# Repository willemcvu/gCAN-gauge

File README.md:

# gCAN-gauge
An open-source ESP32-based programmable digital gauge targeted at EV conversions

See some previews of mechanical stuff and BOM costing here: https://imgur.com/gallery/dh8G9dV/comment/2116424201

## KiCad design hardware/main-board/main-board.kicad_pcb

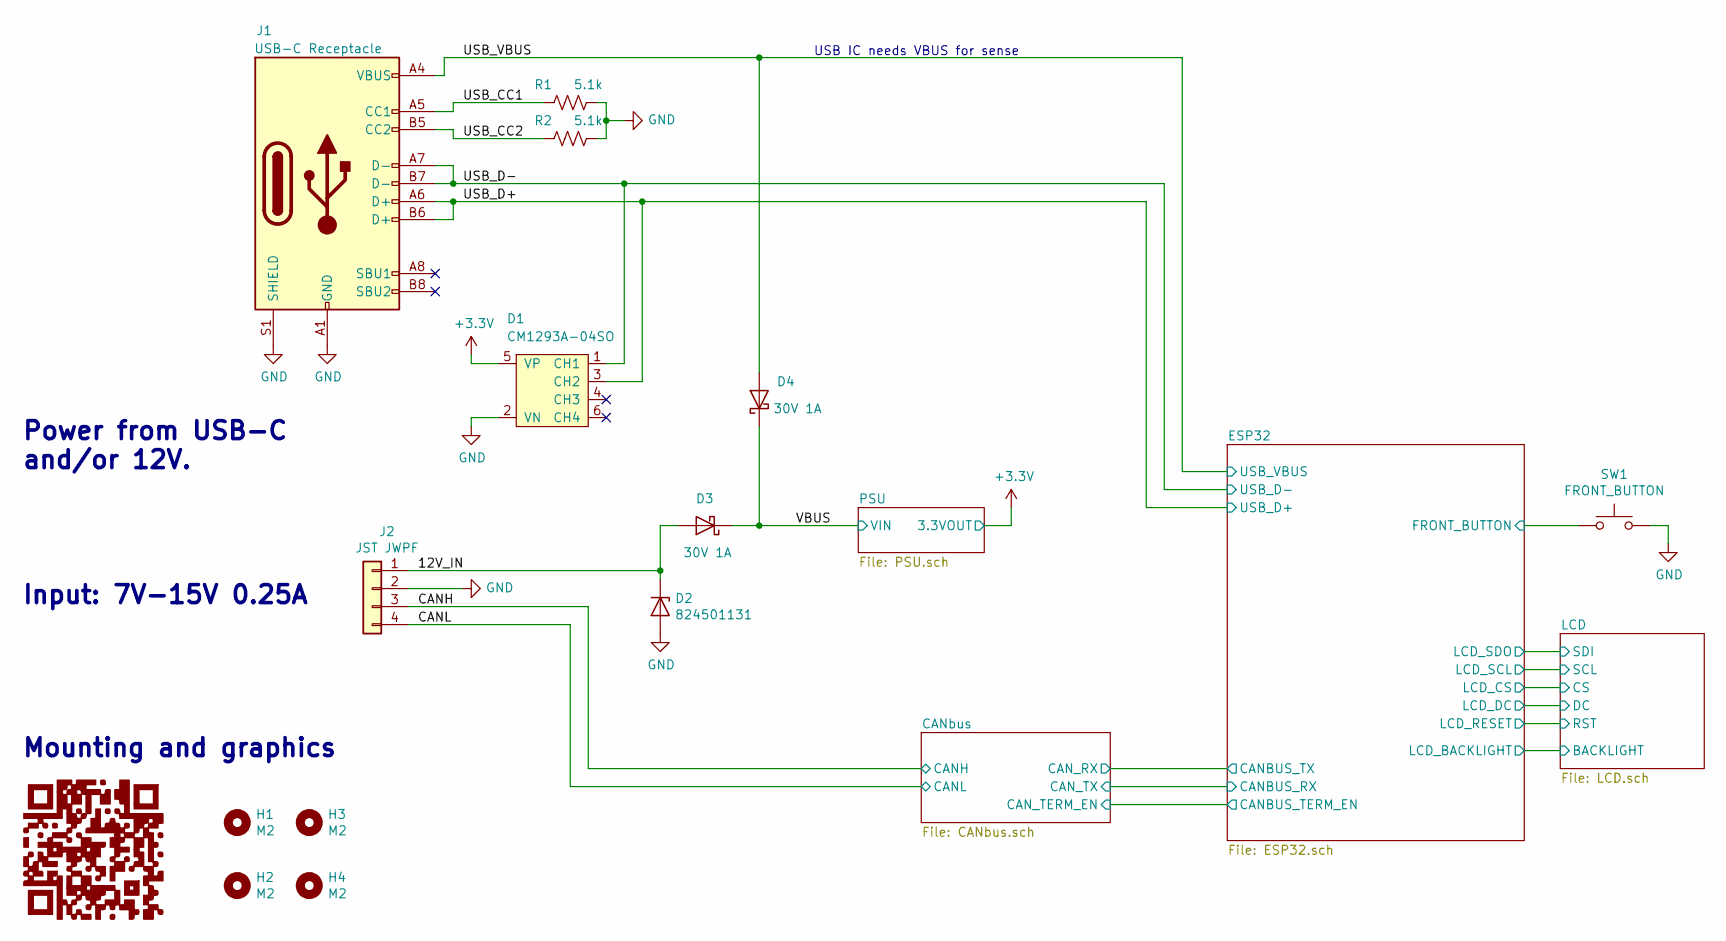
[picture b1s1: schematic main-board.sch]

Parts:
D1: CM1293A-04SO; SOT-23-6; MPN CM1293A-04SO
D2: 824501131; D_SMA; MPN 824501131
D3, D4: 30V 1A; D_SMA; MPN SS13MHRSG
G1: LOGO; gcan-gauge-github-link-qr; MPN DNP
H1, H2, H3, H4: M2; MountingHole_2.1mm; MPN DNP
J1: USB-C Receptacle; USB_C_Receptacle_JAE_DX07S024WJ3R400; MPN DX07S024WJ3R400
J2: JST JWPF; JST_JWPF_B04B-JWPF-SK-R_1x04_P2.00mm_Vertical; MPN B04B-JWPF-SK-R(LF)(SN)
R1, R2: 5.1k; R_0603_1608Metric; MPN RC0603JR-075K1L
SW1: FRONT_BUTTON; SW_SPST_PTS810; MPN B3S-1100P

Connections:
+3V3: D1.5 (VP); also elsewhere on the board
/12V_IN: D2.1 (K), D3.2 (A), J2.1
/CANH: J2.3; also elsewhere on the board
/CANL: J2.4; also elsewhere on the board
/ESP32/FRONT_BUTTON: SW1.1; also elsewhere on the board
/USB_CC1: J1.A5 (CC1), R1.2
/USB_CC2: J1.B5 (CC2), R2.2
/USB_D+: D1.3 (CH2), J1.A6 (D+), J1.B6 (D+); also elsewhere on the board
/USB_D-: D1.1 (CH1), J1.A7 (D-), J1.B7 (D-); also elsewhere on the board
/USB_VBUS: D4.2 (A), J1.A4 (VBUS), J1.A9 (VBUS), J1.B4 (VBUS), J1.B9 (VBUS); also elsewhere on the board
/VBUS: D3.1 (K), D4.1 (K); also elsewhere on the board
GND: D1.2 (VN), D2.2 (A), J1.A1 (GND), J1.A12 (GND), J1.B1 (GND), J1.B12 (GND), J1.S1 (SHIELD), J2.2, R1.1, R2.1, SW1.2; also elsewhere on the board

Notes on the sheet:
Input: 7V-15V 0.25A
Power from USB-C and/or 12V.
Mounting and graphics
USB IC needs VBUS for sense

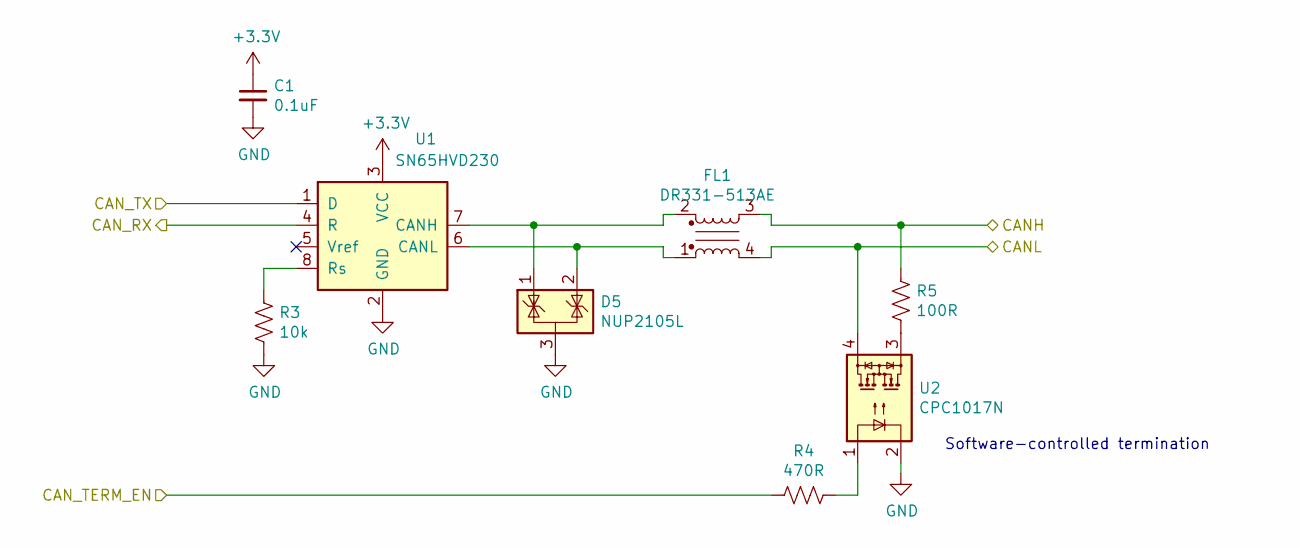
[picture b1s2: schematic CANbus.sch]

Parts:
C1: 0.1uF; C_0603_1608Metric; MPN CL10B104KA8NFNC
D5: NUP2105L; SOT-23; MPN NUP2105LT1G
FL1: DR331-513AE; COMMON_MODE_CHOKE_BOURNS_DR331; MPN DR331-513AE
R3: 10k; R_0603_1608Metric; MPN RC0603JR-0710KL
R4: 470R; R_0603_1608Metric; MPN RC0603JR-07470RL
R5: 100R; R_0603_1608Metric; MPN RC0603JR-07100RL
U1: SN65HVD230; SOIC-8_3.9x4.9mm_P1.27mm; MPN SN65HVD230
U2: CPC1017N; SOP-4_3.8x4.1mm_P2.54mm; MPN CPC1017N

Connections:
+3V3: C1.1, U1.3 (VCC); also elsewhere on the board
/CANH: FL1.3, R5.1; also elsewhere on the board
/CANL: FL1.4, U2.4; also elsewhere on the board
/ESP32/CANBUS_RX: U1.1 (D); also elsewhere on the board
/ESP32/CANBUS_TERM_EN: R4.2; also elsewhere on the board
/ESP32/CANBUS_TX: U1.4 (R); also elsewhere on the board
GND: C1.2, D5.3 (A), R3.2, U1.2 (GND), U2.2; also elsewhere on the board
unnamed: D5.1 (K), FL1.2, U1.7 (CANH)
unnamed: D5.2 (K), FL1.1, U1.6 (CANL)
unnamed: R3.1, U1.8 (Rs)
unnamed: R4.1, U2.1
unnamed: R5.2, U2.3

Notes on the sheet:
Software-controlled termination

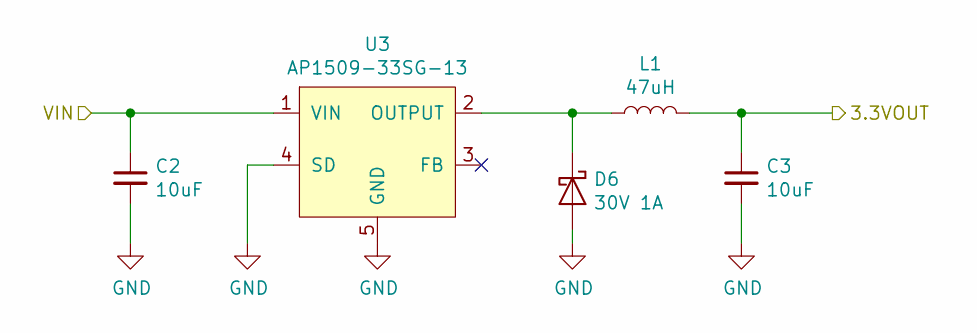
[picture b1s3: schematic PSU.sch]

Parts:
C2: 10uF; C_1210_3225Metric; MPN C1210C106M3RACTU
C3: 10uF; C_0805_2012Metric; MPN CL21B106KQQNFNE
D6: 30V 1A; D_SMA; MPN SS13MHRSG
L1: 47uH; L_Taiyo-Yuden_NR-60xx; MPN NRS6045T470MMGKV
U3: AP1509-33SG-13; SO-8_3.9x4.9mm_P1.27mm; MPN AP1509-33SG-13

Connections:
+3V3: C3.1, L1.2; also elsewhere on the board
/VBUS: C2.1, U3.1 (VIN); also elsewhere on the board
GND: C2.2, C3.2, D6.2 (A), U3.4 (SD), U3.5 (GND), U3.6 (GND), U3.7 (GND), U3.8 (GND); also elsewhere on the board
unnamed: D6.1 (K), L1.1, U3.2 (OUTPUT)

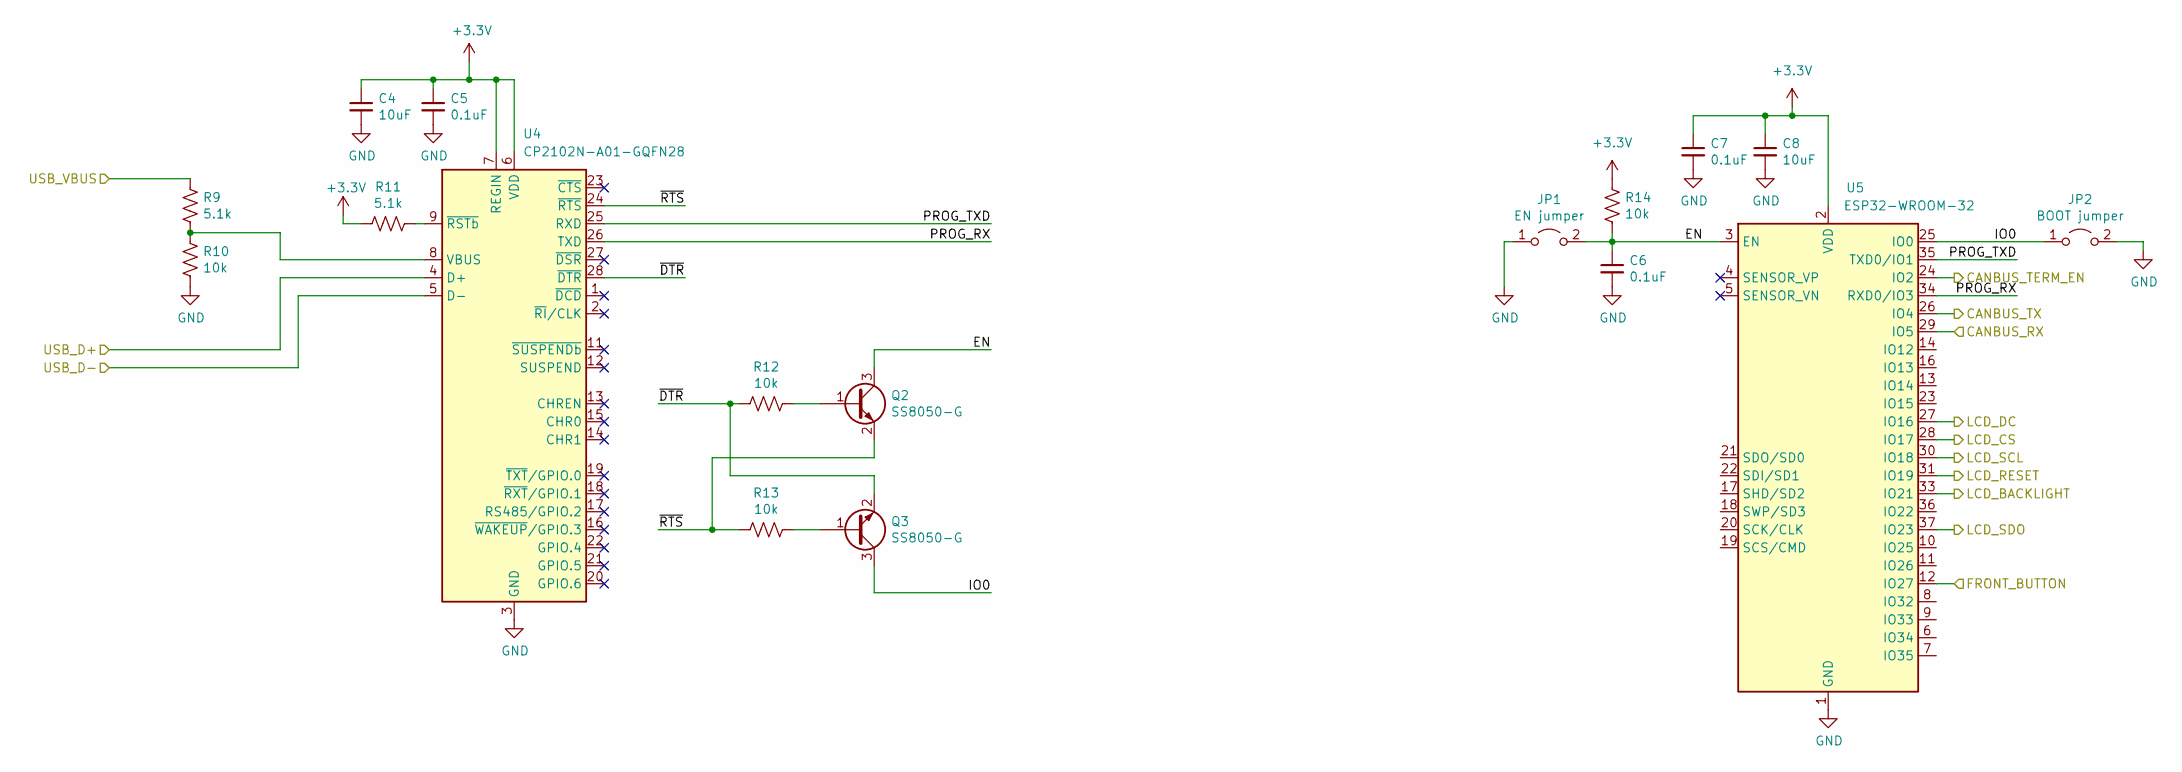
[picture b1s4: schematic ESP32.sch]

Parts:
C4, C8: 10uF; C_0805_2012Metric; MPN CL21B106KQQNFNE
C5, C6, C7: 0.1uF; C_0603_1608Metric; MPN CL10B104KA8NFNC
JP1: EN jumper; SolderJumper-2_P1.3mm_Open_RoundedPad1.0x1.5mm; MPN DNP
JP2: BOOT jumper; SolderJumper-2_P1.3mm_Open_RoundedPad1.0x1.5mm; MPN DNP
Q2, Q3: SS8050-G; SOT-23; MPN SS8050-G
R9, R11: 5.1k; R_0603_1608Metric; MPN RC0603JR-075K1L
R10, R12, R13, R14: 10k; R_0603_1608Metric; MPN RC0603JR-0710KL
U4: CP2102N-A01-GQFN28; QFN-28-1EP_5x5mm_P0.5mm_EP3.35x3.35mm; MPN CP2102N-A01-GQFN28
U5: ESP32-WROOM-32; MPN ESP32-WROOM-32D

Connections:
+3V3: C4.1, C5.1, C7.1, C8.1, R11.2, R14.1, U4.6 (VDD), U4.7 (REGIN), U5.2 (VDD); also elsewhere on the board
/ESP32/CANBUS_RX: U5.29 (IO5); also elsewhere on the board
/ESP32/CANBUS_TERM_EN: U5.24 (IO2); also elsewhere on the board
/ESP32/CANBUS_TX: U5.26 (IO4); also elsewhere on the board
/ESP32/EN: C6.1, JP1.2 (B), Q2.3 (C), R14.2, U5.3 (EN)
/ESP32/FRONT_BUTTON: U5.12 (IO27); also elsewhere on the board
/ESP32/IO0: JP2.1 (A), Q3.3 (C), U5.25 (IO0)
/ESP32/LCD_RESET: U5.31 (IO19); also elsewhere on the board
/ESP32/LCD_SCL: U5.30 (IO18); also elsewhere on the board
/ESP32/LCD_SDO: U5.37 (IO23); also elsewhere on the board
/ESP32/PROG_RX: U4.26 (TXD), U5.34 (RXD0/IO3)
/ESP32/PROG_TXD: U4.25 (RXD), U5.35 (TXD0/IO1)
/ESP32/~DTR: Q3.2 (E), R12.2, U4.28 (~DTR)
/ESP32/~RTS: Q2.2 (E), R13.2, U4.24 (~RTS)
/LCD/BACKLIGHT: U5.33 (IO21); also elsewhere on the board
/LCD/CS: U5.28 (IO17); also elsewhere on the board
/LCD/DC: U5.27 (IO16); also elsewhere on the board
/USB_D+: U4.4 (D+); also elsewhere on the board
/USB_D-: U4.5 (D-); also elsewhere on the board
/USB_VBUS: R9.2; also elsewhere on the board
GND: C4.2, C5.2, C6.2, C7.2, C8.2, JP1.1 (A), JP2.2 (B), R10.1, U4.3 (GND), U4.29 (GND), U5.1 (GND), U5.15 (GND), U5.38 (GND); also elsewhere on the board
unnamed: Q2.1 (B), R12.1
unnamed: Q3.1 (B), R13.1
unnamed: R9.1, R10.2, U4.8 (VBUS)
unnamed: R11.1, U4.9 (~RSTb)

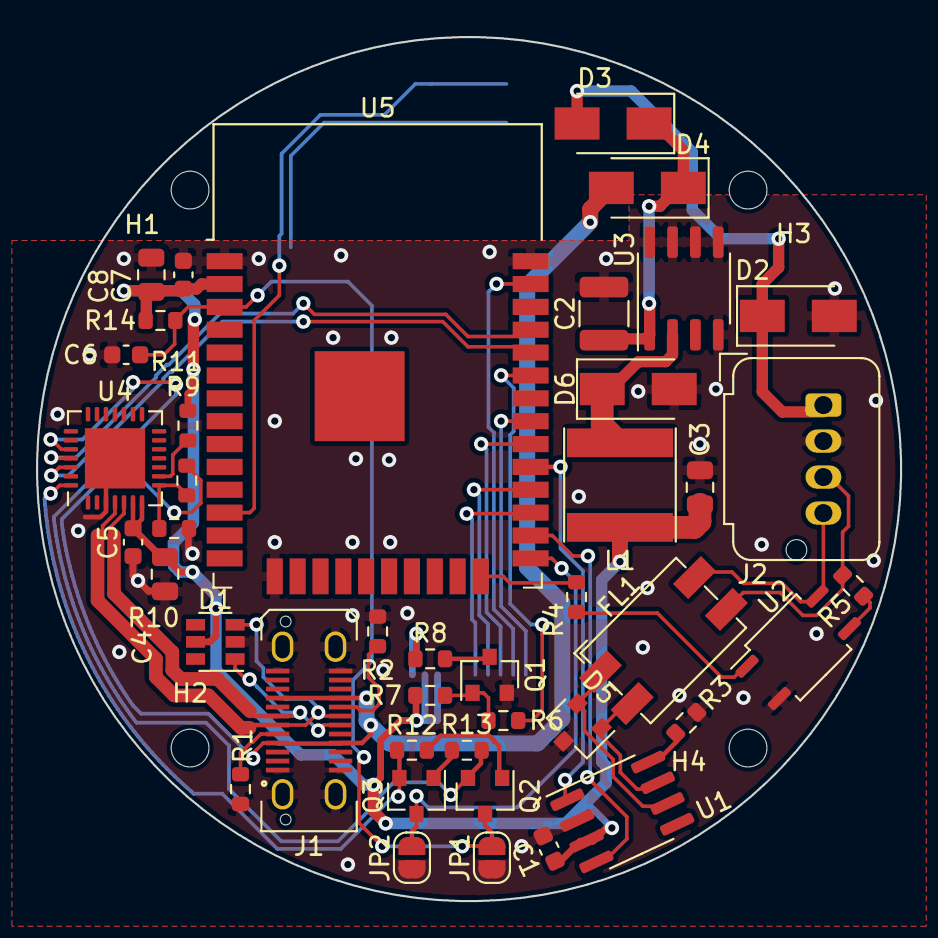
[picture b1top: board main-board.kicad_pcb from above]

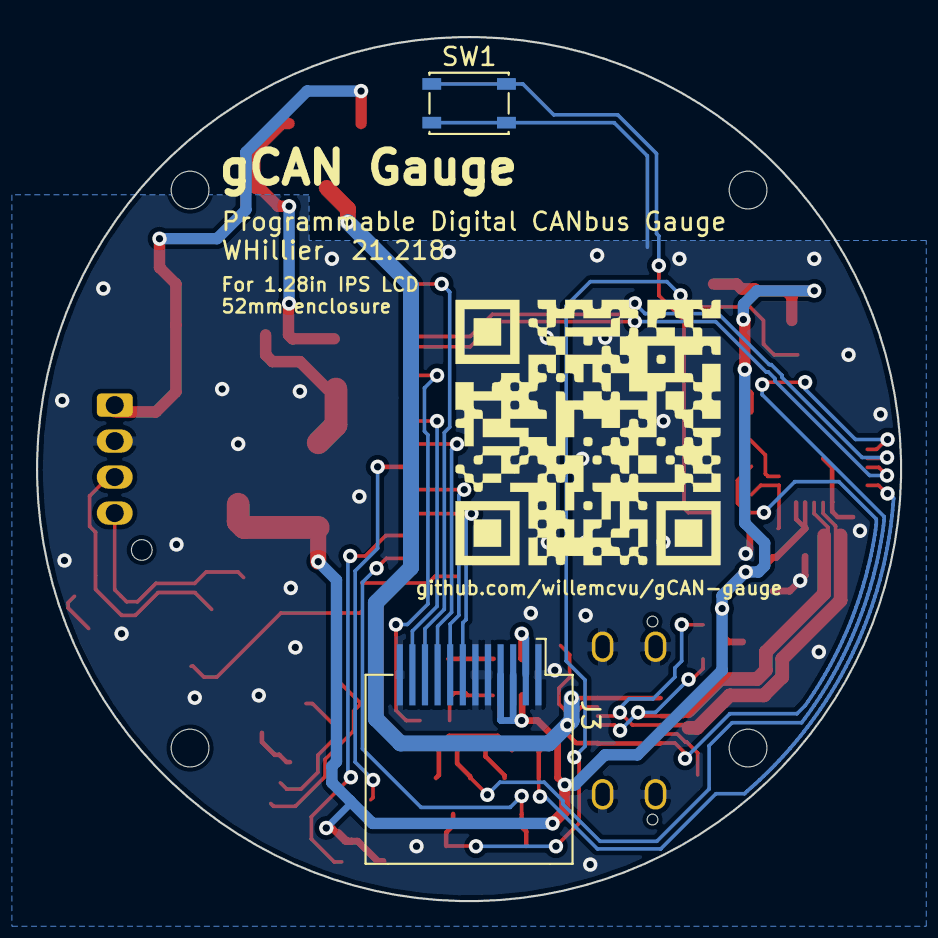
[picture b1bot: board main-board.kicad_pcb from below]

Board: 2 copper layers, 48.0 x 48.0 mm, 49 parts (3 on the bottom side), 40 nets.

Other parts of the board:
J3: LCD_FFC_SOLDER; LCD_ROUND_IPS_ER-TFT1.28-1
Q1: SS8050-G; SOT-23
R6: 1k; R_0603_1608Metric
R7: 10k; R_0603_1608Metric
R8: 10R; R_0603_1608Metric

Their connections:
+3V3: J3.3, J3.4, R7.2; also elsewhere on the board
/ESP32/LCD_RESET: J3.11; also elsewhere on the board
/ESP32/LCD_SCL: J3.9; also elsewhere on the board
/ESP32/LCD_SDO: J3.10; also elsewhere on the board
/LCD/BACKLIGHT: R6.2; also elsewhere on the board
/LCD/CS: J3.8; also elsewhere on the board
/LCD/DC: J3.7; also elsewhere on the board
GND: J3.1, J3.5, J3.6, J3.12, Q1.2; also elsewhere on the board
unnamed: J3.2, R8.1
unnamed: Q1.1, R6.1, R7.1
unnamed: Q1.3, R8.2

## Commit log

2021-07-20 Started basic schematic. Completed schematic for USB-C.
2021-07-20 Added USB to uart
2021-07-21 sch wip
2021-07-23 Sch mostly done, drew a few custom footprints, placement mostly done.
2021-07-31 layout almost done
2021-07-31 added all 3d
2021-07-31 SO-8 3d added, layout done
2021-07-31 fixed wrong smd/tht attribute. exported STEP.
2021-08-01 updated LCD to proper board footprint, added additional 3d models
2021-08-01 added qr code, switched button to a different button. put on reddit for review
2021-08-06 Added mounting holes, tweaked layout to accomodate.
2021-08-06 BOM cleanup/adding MPNs
2021-08-06 further BOM fixing/cleanup for ordering.
2021-08-06 exported gerbers. Shipping 21.218.
2021-08-13 cleaning up BOM
2021-08-13 first code :) currently just sweeps up and then down from 0-100. But a good first test to prove how smooth the display can be at 80MHz SPI.
2021-08-13 Enclosure parts ready to test print
2021-08-22 fw random tests
